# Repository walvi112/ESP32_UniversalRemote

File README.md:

# ESP32 Universal Remote  
A universal remote control powered by ESP32.

## Features

### 🔧 Hardware  
- IR receiver for learning new IR codes  
- 7 IR emitters for all-angle transmission

### 💻 Firmware  
- Web server to send/add new IR commands  
- mDNS service broadcasts the web server at [`remote.local`](http://remote.local)  
- Supports up to 5 different TV command sets  
- Supports up to 50 different IR protocols  
- Easy Wi-Fi setup via AP mode

---

## 🚀 Setup

### 📶 Wi-Fi Setup  
1. On startup, press the **user button** to enter AP mode  
2. Connect to the `esp32remote` Wi-Fi network  
3. In your browser, go to [`remote.local`](http://remote.local)  
4. Enter your Wi-Fi information and click `Submit`

---

### 🔄 Send/Add IR Code

#### ➕ Add IR Code  
1. After setting the Wi-Fi network, go to [`remote.local`](http://remote.local)  
2. Select **Add TV** from the dropdown and choose a remote ID  
3. Click the **Register** button — the LED will start blinking  
4. Point your TV remote at the IR receiver and press a key  
5. If successful, the LED stops blinking; if not, it times out after 5 seconds

#### 📤 Send IR Code  
1. Select **TV Remote** and choose a remote ID from the dropdown  
2. Press the key you want to send

---

### 🐞 Debugging

- Use a serial monitor with **baud rate: 115200** to view logs  
- You can also send serial commands to the device

#### 🔧 Serial Commands  
| Command | Description |
|--------|-------------|
| `led on` | Turn on the LED |
| `led off` | Turn off the LED |
| `send ir _protocol _address _command` | Send IR code (all values in decimal). Refer to `irmpprotocols.h` for `_protocol` values |
| `set wifi _ssid+_pwd` | Set Wi-Fi SSID and password |
| `add tv ir _ir_code _remote_id` | Add new IR command to `_remote_id`. LED will blink while waiting for input |
| `reset wifi` | Enter AP mode (same as pressing user button) |
| `restart` | Restart the device |

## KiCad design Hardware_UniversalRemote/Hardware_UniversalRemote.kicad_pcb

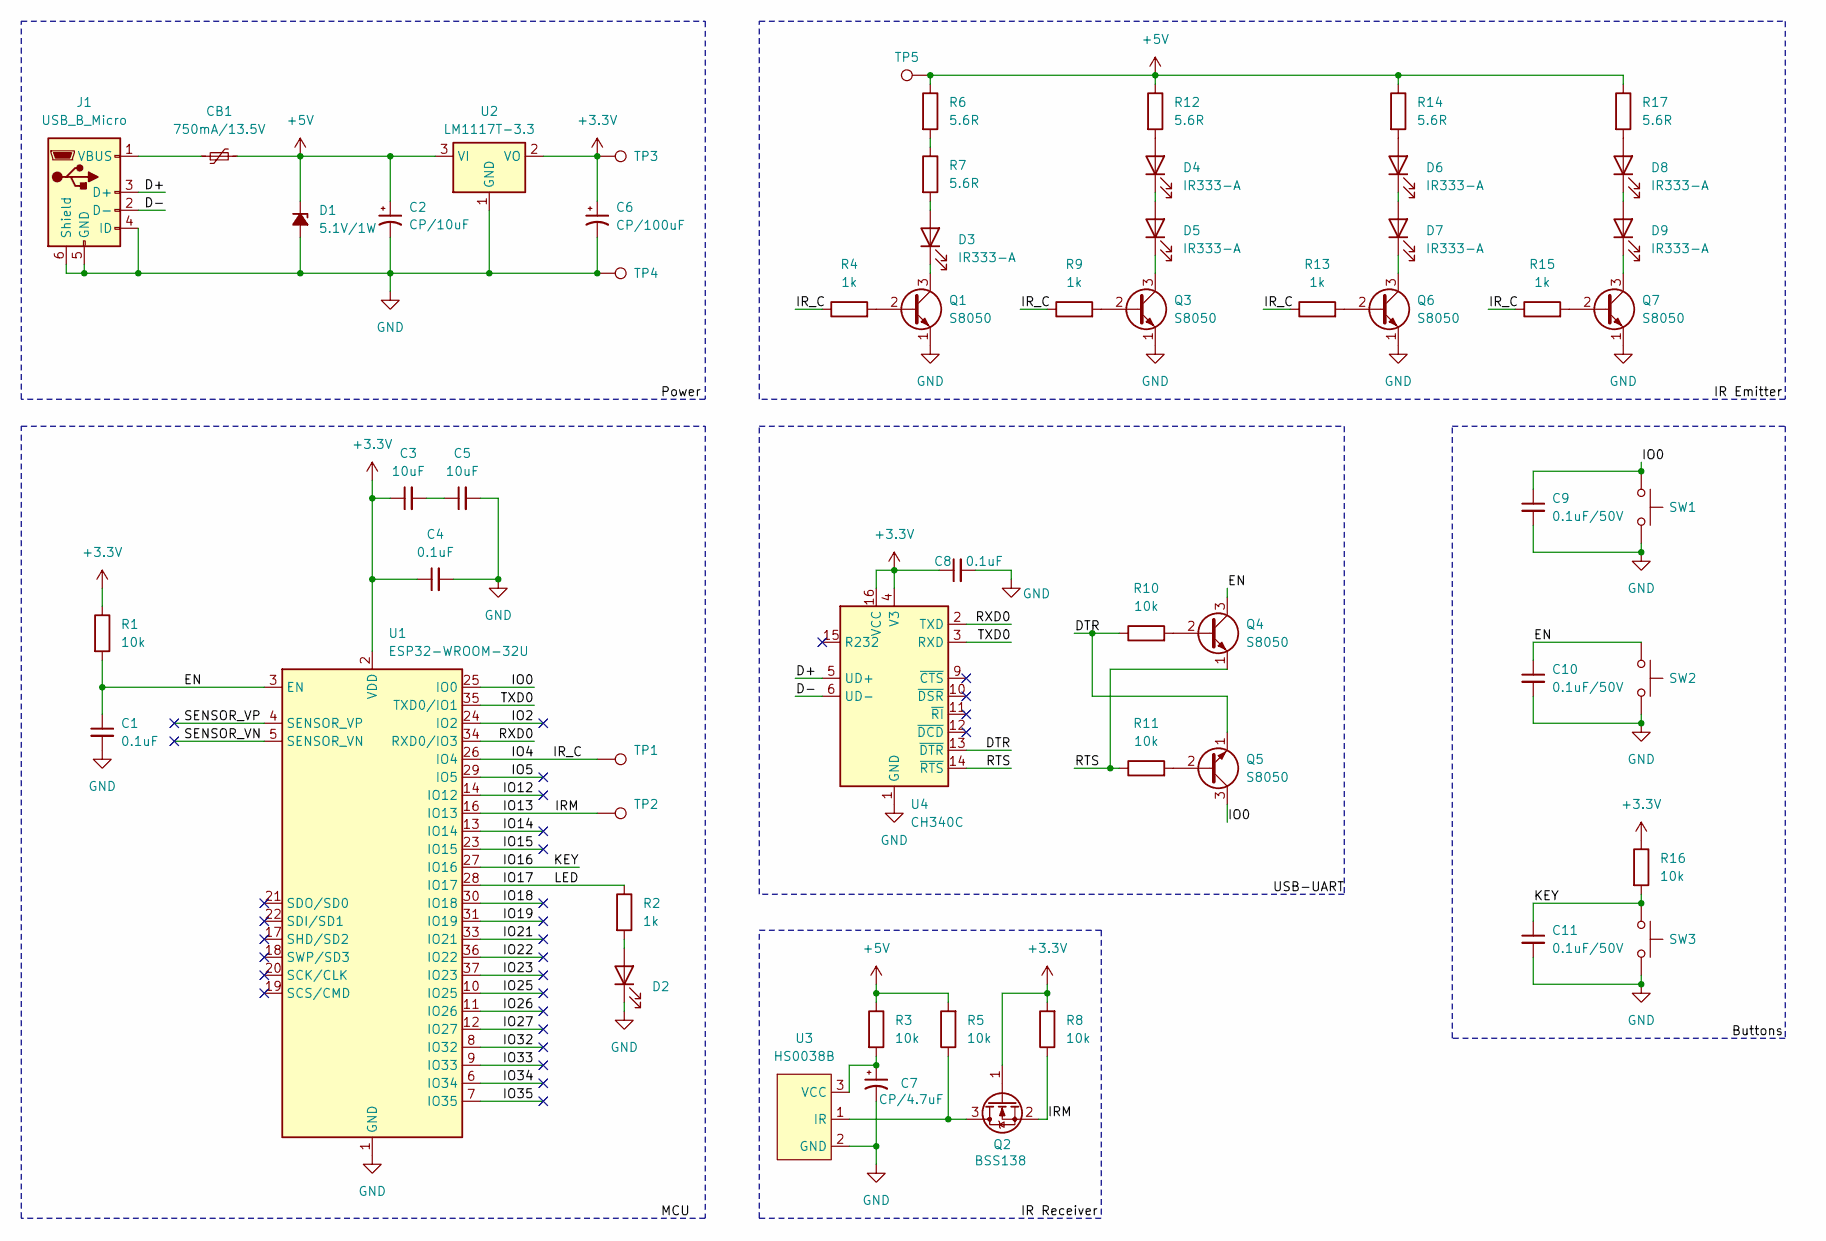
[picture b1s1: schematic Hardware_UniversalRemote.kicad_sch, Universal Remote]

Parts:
C1, C4, C8: 0.1uF; C_Disc_D3.4mm_W2.1mm_P2.50mm
C2: CP/10uF; CP_Radial_D5.0mm_P2.00mm
C3, C5: 10uF; CP_Radial_D4.0mm_P2.00mm
C6: CP/100uF; CP_Radial_D8.0mm_P3.50mm
C7: CP/4.7uF; CP_Radial_D5.0mm_P2.00mm
C9, C10, C11: 0.1uF/50V; C_Disc_D3.4mm_W2.1mm_P2.50mm
CB1: 750mA/13.5V; Fuse_1812_4532Metric_Pad1.30x3.40mm_HandSolder
D1: 5.1V/1W; D_DO-41_SOD81_P7.62mm_Horizontal
D2: LED; LED_D3.0mm
D3: IR333-A; LED_D5.0mm
D4, D5, D6, D7, D8, D9: IR333-A; LED_D5.0mm_Horizontal_O3.81mm_Z9.0mm
J1: USB_B_Micro; USB_Micro-B_Wuerth_629105150521
Q1, Q3, Q4, Q5, Q6, Q7: S8050; TO-92_Inline
Q2: BSS138; SOT-23
R1, R3, R5, R8, R10, R11, R16: 10k; R_Axial_DIN0207_L6.3mm_D2.5mm_P7.62mm_Horizontal
R2, R4, R9, R13, R15: 1k; R_Axial_DIN0207_L6.3mm_D2.5mm_P7.62mm_Horizontal
R6, R7, R12, R14, R17: 5.6R; R_Axial_DIN0414_L11.9mm_D4.5mm_P15.24mm_Horizontal
SW1, SW2, SW3: SW_Push; SW_TH_Tactile_Omron_B3F-10xx
TP1, TP2, TP3, TP4, TP5: TestPoint; TestPoint_Pad_D2.5mm
U1: ESP32-WROOM-32U
U2: LM1117T-3.3; TO-220-3_Horizontal_TabDown
U3: HS0038B; TO-92_Inline_Wide
U4: CH340C; SOIC-16_3.9x9.9mm_P1.27mm

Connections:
+3.3V: C3.1, C4.1, C6.1, C8.1, Q2.1 (G), R1.1, R8.2, R16.1, TP3.1, U1.2 (VDD), U2.2 (VO), U4.4 (V3), U4.16 (VCC)
+5V: C2.1, CB1.2, D1.1 (K), R3.1, R5.2, R6.1, R12.1, R14.1, R17.1, TP5.1, U2.3 (VI)
/D+: J1.3 (D+), U4.5 (UD+)
/D-: J1.2 (D-), U4.6 (UD-)
/DTR: Q5.1 (E), R10.1, U4.13 (~DTR)
/EN: C1.1, C10.1, Q4.3 (C), R1.2, SW2.1, U1.3 (EN)
/IO0: C9.1, Q5.3 (C), SW1.1, U1.25 (IO0)
/IO2: U1.24 (IO2)
/IO4: R4.1, R9.1, R13.1, R15.1, TP1.1, U1.26 (IO4)
/IO5: U1.29 (IO5)
/IO12: U1.14 (IO12)
/IO13: Q2.2 (S), R8.1, TP2.1, U1.16 (IO13)
/IO14: U1.13 (IO14)
/IO15: U1.23 (IO15)
/IO16: C11.1, R16.2, SW3.1, U1.27 (IO16)
/IO17: R2.1, U1.28 (IO17)
/IO18: U1.30 (IO18)
/IO19: U1.31 (IO19)
/IO21: U1.33 (IO21)
/IO22: U1.36 (IO22)
/IO23: U1.37 (IO23)
/IO25: U1.10 (IO25)
/IO26: U1.11 (IO26)
/IO27: U1.12 (IO27)
/IO32: U1.8 (IO32)
/IO33: U1.9 (IO33)
/IO34: U1.6 (IO34)
/IO35: U1.7 (IO35)
/RTS: Q4.1 (E), R11.1, U4.14 (~RTS)
/RXD0: U1.34 (RXD0/IO3), U4.2 (TXD)
/SENSOR_VN: U1.5 (SENSOR_VN)
/SENSOR_VP: U1.4 (SENSOR_VP)
/TXD0: U1.35 (TXD0/IO1), U4.3 (RXD)
GND: C1.2, C2.2, C4.2, C5.2, C6.2, C7.2, C8.2, C9.2, C10.2, C11.2, D1.2 (A), D2.1 (K), J1.4 (ID), J1.5 (GND), J1.6 (Shield), Q1.1 (E), Q3.1 (E), Q6.1 (E), Q7.1 (E), SW1.2, SW2.2, SW3.2, TP4.1, U1.1 (GND), U1.15 (GND), U1.38 (GND), U1.39 (GND), U2.1 (GND), U3.2 (GND), U4.1 (GND)
unnamed: C3.2, C5.1
unnamed: D2.2 (A), R2.2
unnamed: D3.2 (A), R7.2
unnamed: D3.1 (K), Q1.3 (C)
unnamed: D4.2 (A), R12.2
unnamed: D4.1 (K), D5.2 (A)
unnamed: D5.1 (K), Q3.3 (C)
unnamed: D6.2 (A), R14.2
unnamed: D6.1 (K), D7.2 (A)
unnamed: D7.1 (K), Q6.3 (C)
unnamed: D8.2 (A), R17.2
unnamed: D8.1 (K), D9.2 (A)
unnamed: D9.1 (K), Q7.3 (C)
unnamed: CB1.1, J1.1 (VBUS)
unnamed: Q1.2 (B), R4.2
unnamed: Q2.3 (D), R5.1, U3.1 (IR)
unnamed: Q3.2 (B), R9.2
unnamed: Q4.2 (B), R10.2
unnamed: Q5.2 (B), R11.2
unnamed: Q6.2 (B), R13.2
unnamed: Q7.2 (B), R15.2
unnamed: R6.2, R7.1
unnamed: C7.1, R3.2, U3.3 (VCC)

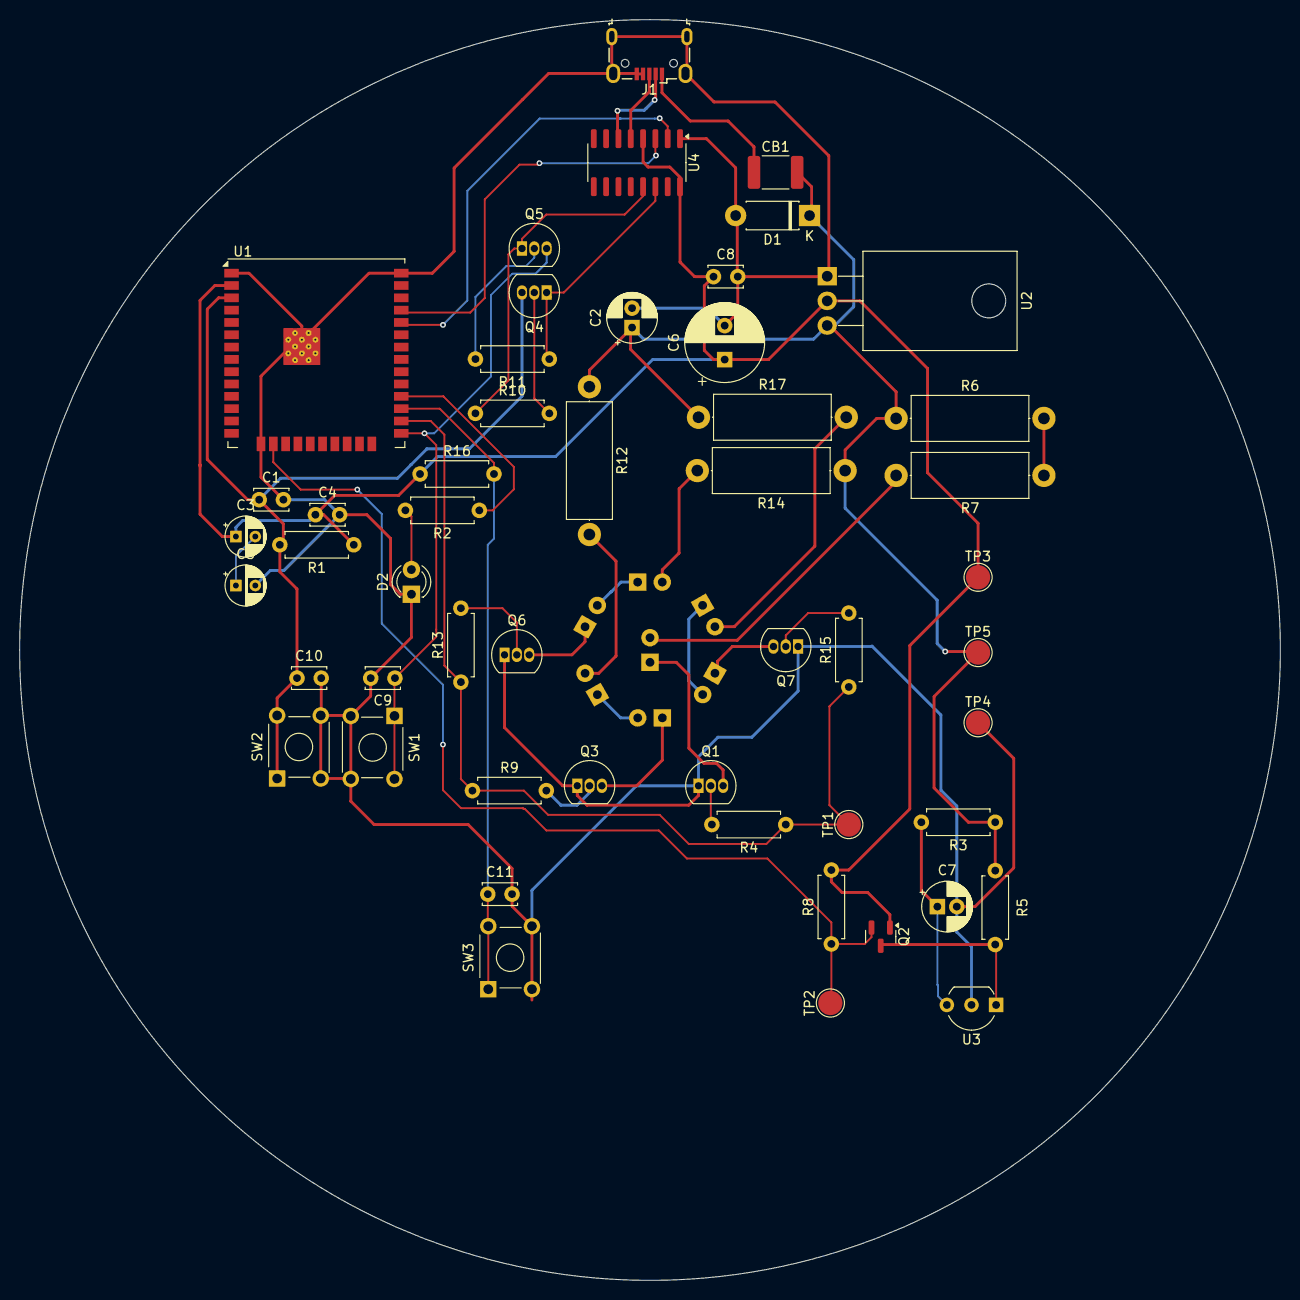
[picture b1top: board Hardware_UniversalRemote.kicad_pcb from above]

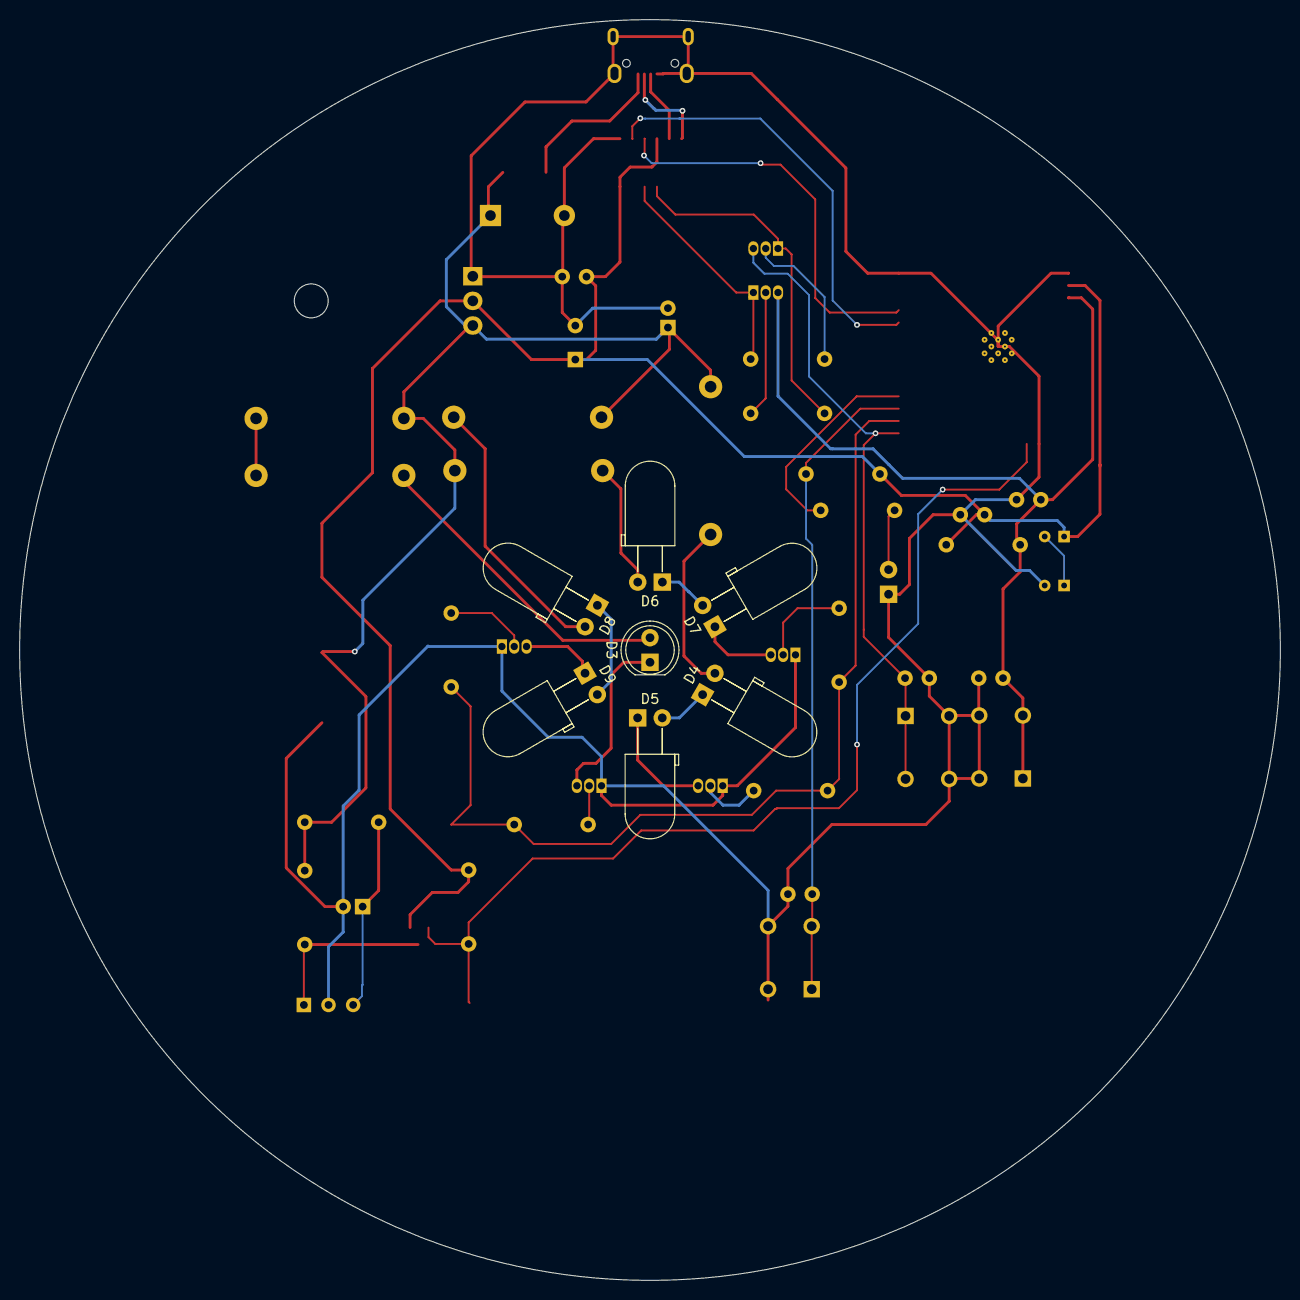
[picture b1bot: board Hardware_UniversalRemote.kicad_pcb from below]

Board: 2 copper layers, 130.0 x 130.0 mm, 58 parts (7 on the bottom side), 38 nets.

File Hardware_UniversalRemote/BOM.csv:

"Reference","Value","Datasheet","Footprint","Qty","DNP"
"C1,C4,C8","0.1uF","~","Capacitor_THT:C_Disc_D3.4mm_W2.1mm_P2.50mm","3",""
"C2","CP/10uF","~","Capacitor_THT:CP_Radial_D5.0mm_P2.00mm","1",""
"C3,C5","10uF","~","Capacitor_THT:CP_Radial_D4.0mm_P2.00mm","2",""
"C6","CP/100uF","~","Capacitor_THT:CP_Radial_D8.0mm_P3.50mm","1",""
"C7","CP/4.7uF","~","Capacitor_THT:CP_Radial_D5.0mm_P2.00mm","1",""
"C9,C10,C11","0.1uF/50V","~","Capacitor_THT:C_Disc_D3.4mm_W2.1mm_P2.50mm","3",""
"CB1","750mA/13.5V","~","Fuse:Fuse_1812_4532Metric_Pad1.30x3.40mm_HandSolder","1",""
"D1","5.1V/1W","~","Diode_THT:D_DO-41_SOD81_P7.62mm_Horizontal","1",""
"D2","LED","~","LED_THT:LED_D3.0mm","1",""
"D3,D4,D5,D6,D7,D8,D9","IR333-A","~","LED_THT:LED_D5.0mm","7",""
"J1","USB_B_Micro","~","Connector_USB:USB_Micro-B_Wuerth_629105150521","1",""
"Q1,Q3,Q4,Q5,Q6,Q7","S8050","http://www.unisonic.com.tw/datasheet/S8050.pdf","Package_TO_SOT_THT:TO-92_Inline","6",""
"Q2","BSS138","https://www.onsemi.com/pub/Collateral/BSS138-D.PDF","Package_TO_SOT_SMD:SOT-23","1",""
"R1,R3,R5,R8,R10,R11,R16","10k","~","Resistor_THT:R_Axial_DIN0207_L6.3mm_D2.5mm_P7.62mm_Horizontal","7",""
"R2,R4,R9,R13,R15","1k","~","Resistor_THT:R_Axial_DIN0207_L6.3mm_D2.5mm_P7.62mm_Horizontal","5",""
"R6,R7,R12,R14,R17","5.6R","~","Resistor_THT:R_Axial_DIN0414_L11.9mm_D4.5mm_P15.24mm_Horizontal","5",""
"SW1,SW2,SW3","SW_Push","~","Button_Switch_THT:SW_TH_Tactile_Omron_B3F-10xx","3",""
"TP1,TP2,TP3,TP4,TP5","TestPoint","~","TestPoint:TestPoint_Pad_D2.5mm","5",""
"U1","ESP32-WROOM-32U","https://www.espressif.com/sites/default/files/documentation/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","RF_Module:ESP32-WROOM-32U","1",""
"U2","LM1117T-3.3","http://www.ti.com/lit/ds/symlink/lm1117.pdf","Package_TO_SOT_THT:TO-220-3_Horizontal_TabDown","1",""
"U3","HS0038B","","Package_TO_SOT_THT:TO-92_Inline_Wide","1",""
"U4","CH340C","https://datasheet.lcsc.com/szlcsc/Jiangsu-Qin-Heng-CH340C_C8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","Package_SO:SOIC-16_3.9x9.9mm_P1.27mm","1",""

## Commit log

2025-01-06 add power block
2025-01-06 add IR emitter block
2025-01-07 add mcu
2025-01-07 add buttons and usb-uart block
2025-01-08 add mcu and ir receiver block
2025-01-08 add capacitor footprint
2025-01-09 add net list
2025-01-09 fix regulator voltage
2025-01-10 add first pcb layout
2025-01-12 add first pcb layout version
2025-01-13 improve layout
2025-01-14 modify layout
2025-01-14 modify routing
2025-01-15 add trace
2025-01-15 finished second pcb layout
2025-01-29 add pdf for schematic v1
2025-02-03 add esp-idf firmware project
2025-02-23 fix txd/rxd routing for mcu flashing
2025-03-03 fix alignment
2025-03-04 add test firmware
2025-03-05 add wifi_connect function
2025-03-07 add wifi ap and webserver
2025-03-09 remove gpio_config_t due to unknown error
2025-03-09 pulled module irmp_irsnd update
2025-03-09 switch to wifi sta mode and add favicon
2025-03-10 add mDNS dependency
2025-03-10 add mdns service for webserver
2025-03-10 add ac_remote html page
2025-03-11 add dropbox for diferent ir codes
2025-03-11 fix bug function str_to_parram_int
2025-03-12 modify event handler for wifi
2025-03-14 ir_storage_init_function
2025-03-18 fix change wifi bug
2025-03-19 fix wrong wifi ssid input length
2025-03-22 add save wifi information in nvs
2025-03-27 modify set wifi seperator character to account for spaces in ssid
2025-03-29 disable ac remote, add add tv feature to html
2025-04-01 add send ir function from webserver
2025-04-08 fix tiner create error args
2025-04-08 add ir receiver task
2025-04-09 add ir code receive
2025-04-09 fix index error of remote_id
2025-04-10 add debounce function for btn
2025-04-11 fix bug device reset when change wifi parameter
2025-04-12 fix stick hover button when displaying on webkit
2025-04-13 add wifi AP mode
2025-04-14 add login page in AP mode
2025-04-15 increase max_uri_handler to 10
2025-04-15 increase key_press_task stack size
2025-04-15 connect set_wifi function with webserver
2025-04-16 add url_decode function
2025-04-17 refactor webserver module
2025-04-17 restrict /wifi to AP mode and /tv to STA mode
2025-04-19 add demo photo
2025-04-19 add login page and addTV demo photo
